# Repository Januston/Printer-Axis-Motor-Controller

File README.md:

# Printer-Axis-Motor-Controller
👨‍🔬 Custom PCB for printer axis motor control. Features a color-striped disk &amp; light sensor for signal conversion, D flip-flops for bit storage, and logic gates designed via Karnaugh maps. Seamlessly drives printer motors, showcasing electronics in real-world application. Explore &amp; contribute! 🖨️🔧

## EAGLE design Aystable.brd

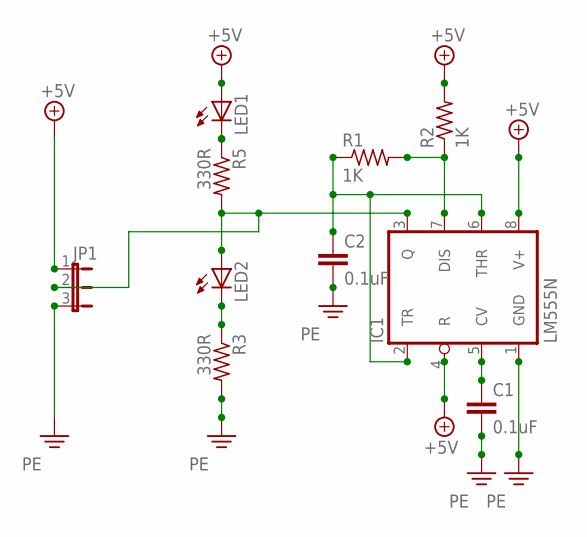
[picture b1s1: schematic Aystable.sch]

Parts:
C1, C2: 0.1uF; C075-032X103
IC1: LM555N; DIL08
JP1: JP2E; JP2
LED1, LED2: LED5MM
R1, R2: 1K; 0207/10
R3, R5: 330R; 0207/10

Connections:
+5V: IC1.4 (R), IC1.8 (V+), JP1.1, LED1.A, R2.2
unnamed: IC1.3 (Q), JP1.2, LED2.A, R5.2
unnamed: C2.1, IC1.2 (TR), IC1.6 (THR), R1.1
unnamed: C1.1, IC1.5 (CV)
unnamed: IC1.7 (DIS), R1.2, R2.1
unnamed: LED1.K (C), R5.1
unnamed: LED2.K (C), R3.1
PE: C1.2, C2.2, IC1.1 (GND), JP1.3, R3.2

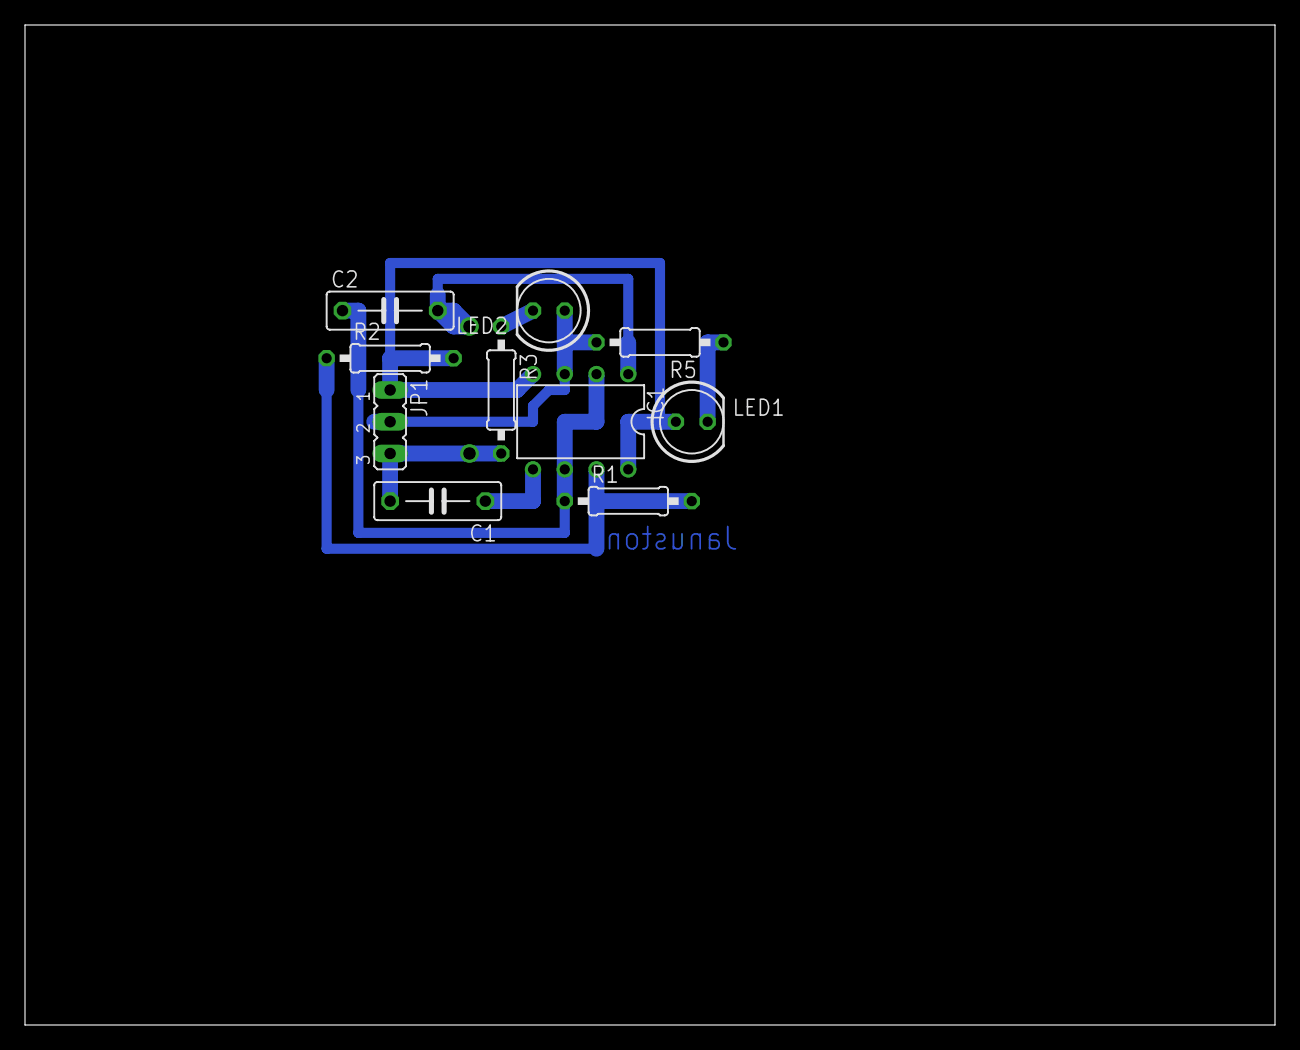
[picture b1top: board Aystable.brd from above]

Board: 2 copper layers, 100.0 x 80.0 mm, 10 parts (0 on the bottom side), 8 nets.

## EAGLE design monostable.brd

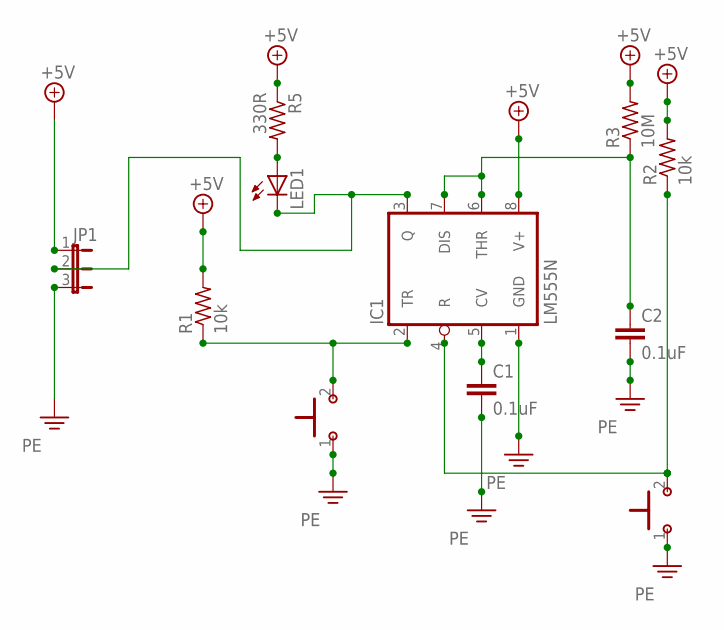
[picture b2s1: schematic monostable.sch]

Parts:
C1, C2: 0.1uF; C075-032X103
IC1: LM555N; DIL08
JP1: JP2E; JP2
LED1: LED5MM
R1, R2: 10k; 0207/10
R3: 10M; 0207/10
R5: 330R; 0207/10
U$1, U$2: PUSHBUTTON

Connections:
+5V: IC1.8 (V+), JP1.1, R1.2, R2.2, R3.2, R5.1
unnamed: IC1.2 (TR), R1.1, U$1.2
unnamed: IC1.4 (R), R2.1, U$2.2
unnamed: C1.1, IC1.5 (CV)
unnamed: C2.1, IC1.6 (THR), IC1.7 (DIS), R3.1
unnamed: IC1.3 (Q), JP1.2, LED1.K (C)
unnamed: LED1.A, R5.2
PE: C1.2, C2.2, IC1.1 (GND), JP1.3, U$1.1, U$2.1

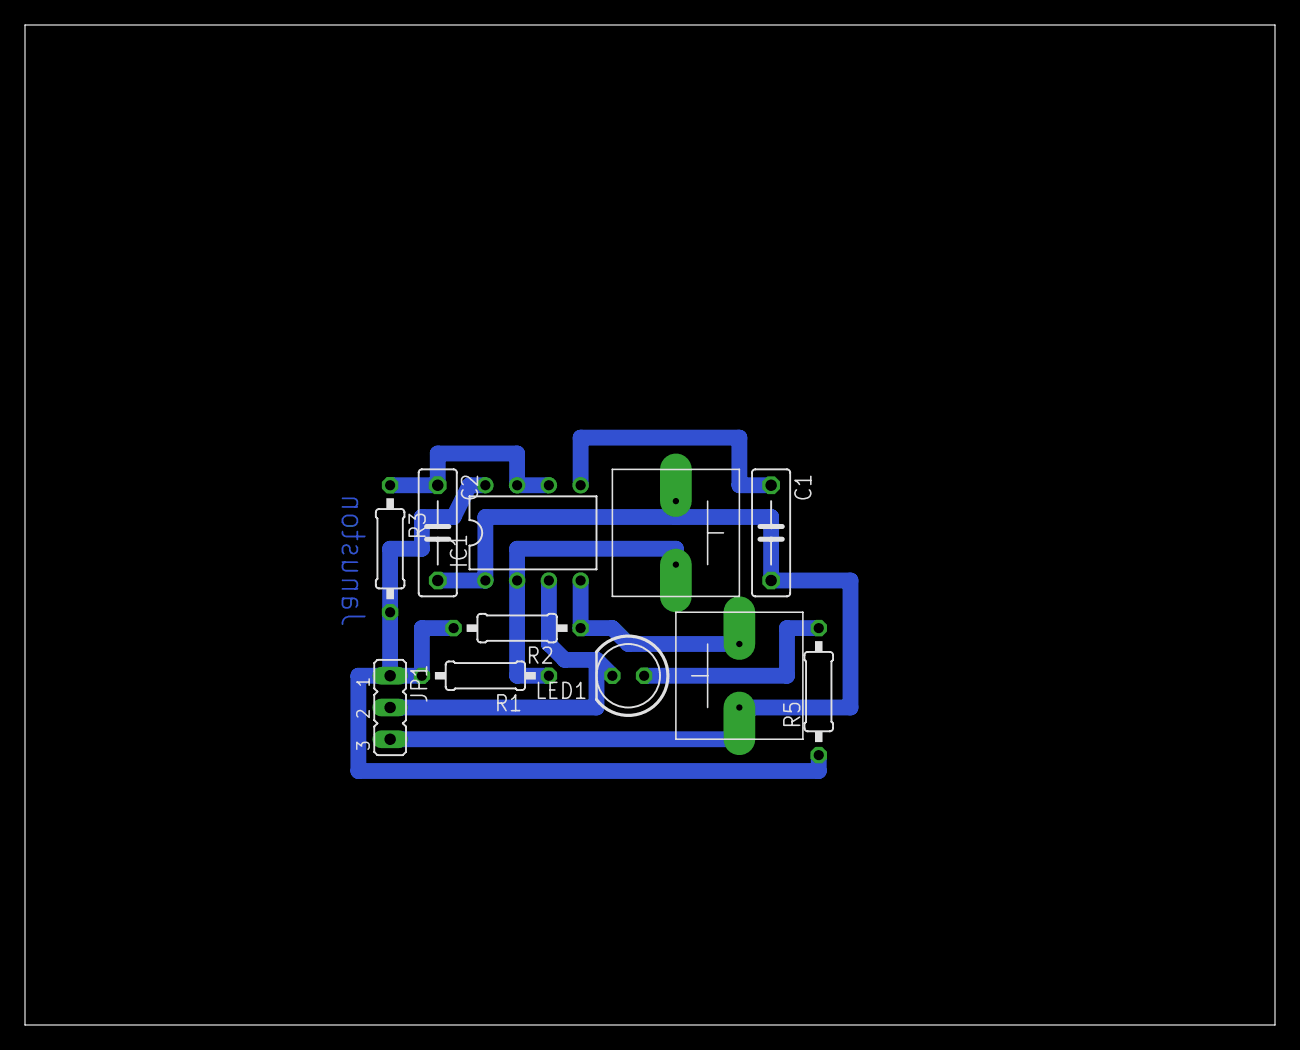
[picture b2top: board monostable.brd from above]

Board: 2 copper layers, 100.0 x 80.0 mm, 11 parts (0 on the bottom side), 8 nets.

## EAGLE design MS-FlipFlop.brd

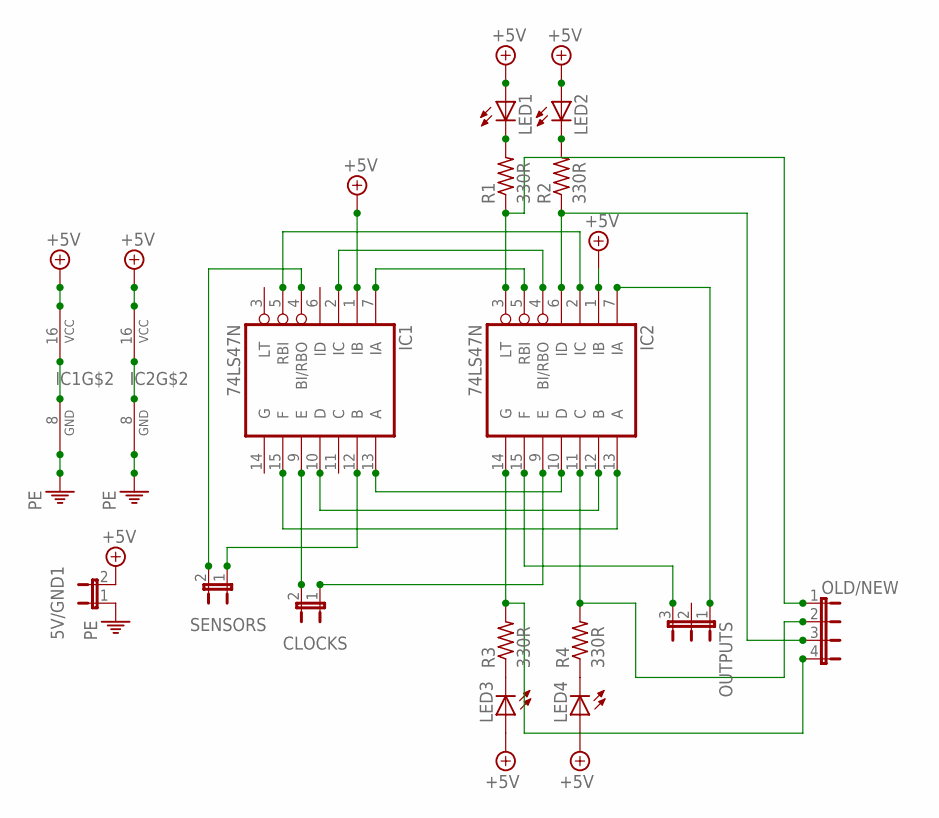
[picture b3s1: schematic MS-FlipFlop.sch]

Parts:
5V/GND1: JP1E; JP1
CLOCKS: JP1E; JP1
IC1, IC2: 74LS47N; DIL16
LED1, LED2, LED3, LED4: LED5MM
OLD/NEW: JP4E; JP4
OUTPUTS: JP2E; JP2
R1, R2, R3, R4: 330R; 0207/10
SENSORS: JP1E; JP1

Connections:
+5V: 5V/GND1.2, IC1.1 (IB), IC1.16 (VCC), IC2.1 (IB), IC2.16 (VCC), LED1.A, LED2.A, LED3.A, LED4.A
unnamed: IC1.2 (IC), IC2.4 (BI/RBO)
unnamed: IC1.5 (RBI), IC2.2 (IC)
unnamed: IC1.7 (IA), IC2.5 (RBI)
unnamed: IC1.10 (D), IC2.12 (B)
unnamed: IC1.13 (A), IC2.10 (D)
unnamed: IC1.15 (F), IC2.13 (A)
unnamed: IC2.3 (LT), OLD/NEW.1, R1.1
unnamed: LED1.K (C), R1.2
unnamed: LED2.K (C), R2.2
unnamed: IC2.6 (ID), OLD/NEW.3, R2.1
unnamed: LED3.K (C), R3.1
unnamed: LED4.K (C), R4.1
unnamed: IC2.14 (G), OLD/NEW.4, R3.2
unnamed: IC2.11 (C), OLD/NEW.2, R4.2
unnamed: CLOCKS.2, IC1.9 (E)
unnamed: CLOCKS.1, IC2.9 (E)
unnamed: IC1.4 (BI/RBO), SENSORS.2
unnamed: IC1.12 (B), SENSORS.1
unnamed: IC2.15 (F), OUTPUTS.3
unnamed: IC2.7 (IA), OUTPUTS.1
PE: 5V/GND1.1, IC1.8 (GND), IC2.8 (GND)

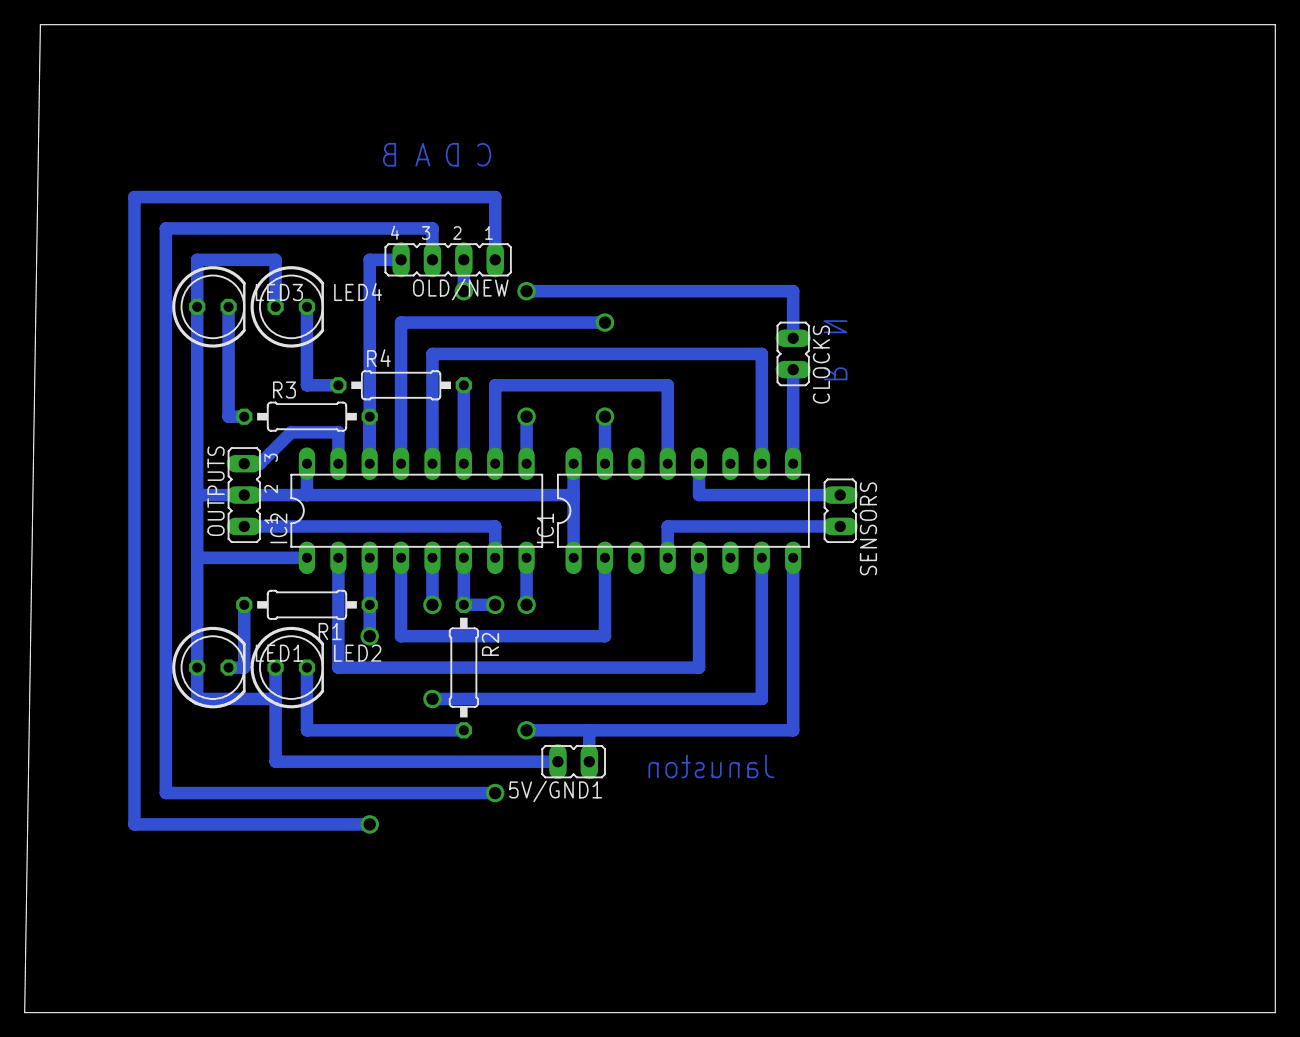
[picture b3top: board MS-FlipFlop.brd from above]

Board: 2 copper layers, 101.3 x 80.0 mm, 15 parts (0 on the bottom side), 22 nets.

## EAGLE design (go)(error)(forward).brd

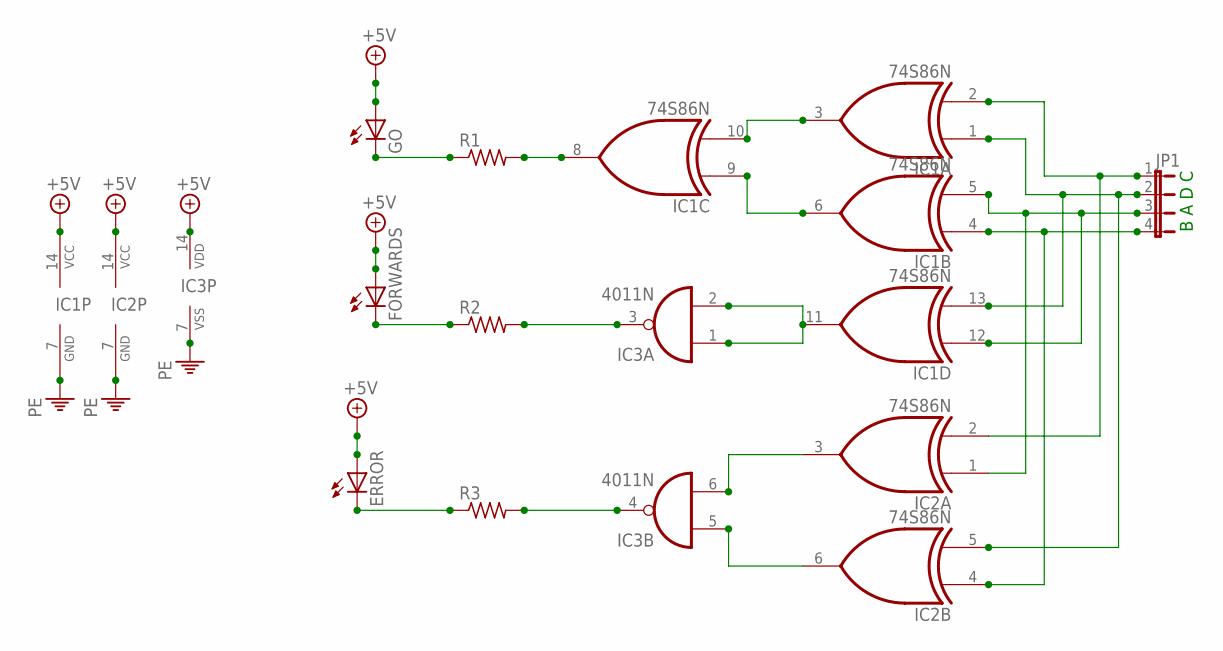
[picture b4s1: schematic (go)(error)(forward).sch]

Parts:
ERROR: LED5MM
FORWARDS: LED5MM
GO: LED5MM
IC1, IC2: 74S86N; DIL14
IC3: 4011N; DIL14
JP1: JP4E; JP4
R1, R2, R3: R-US_0207/10; 0207/10

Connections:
+5V: ERROR.A, FORWARDS.A, GO.A, IC1.14 (VCC), IC2.14 (VCC), IC3.14 (VDD)
unnamed: IC1.2 (I1), IC2.2 (I1), JP1.1
unnamed: IC2.3 (O), IC3.6 (I1)
unnamed: IC1.5 (I1), IC1.12 (I0), IC2.1 (I0), JP1.3
unnamed: IC1.4 (I0), IC2.4 (I0), JP1.4
unnamed: IC2.6 (O), IC3.5 (I0)
unnamed: IC3.3 (O), R2.2
unnamed: IC1.3 (O), IC1.10 (I1)
unnamed: IC1.6 (O), IC1.9 (I0)
unnamed: IC1.1 (I0), IC1.13 (I1), IC2.5 (I1), JP1.2
unnamed: IC1.8 (O), R1.2
unnamed: IC3.4 (O), R3.2
unnamed: GO.K (C), R1.1
unnamed: FORWARDS.K (C), R2.1
unnamed: IC1.11 (O), IC3.1 (I0), IC3.2 (I1)
unnamed: ERROR.K (C), R3.1
PE: IC1.7 (GND), IC2.7 (GND), IC3.7 (VSS)

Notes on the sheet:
B A D C

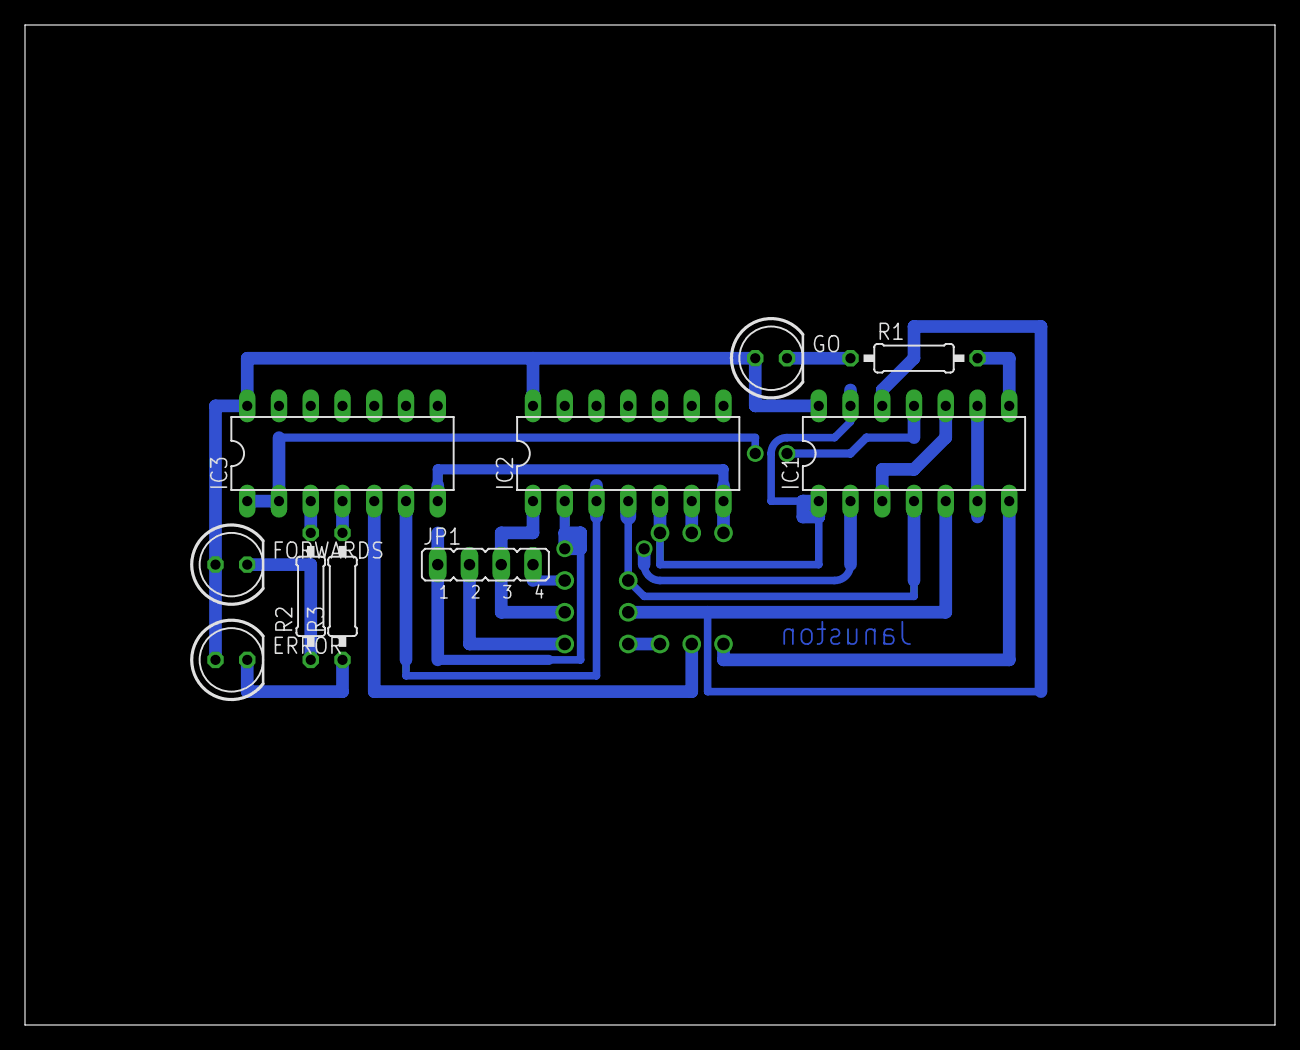
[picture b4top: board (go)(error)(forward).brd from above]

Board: 2 copper layers, 100.0 x 80.0 mm, 10 parts (0 on the bottom side), 17 nets.

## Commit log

2023-09-24 add files
